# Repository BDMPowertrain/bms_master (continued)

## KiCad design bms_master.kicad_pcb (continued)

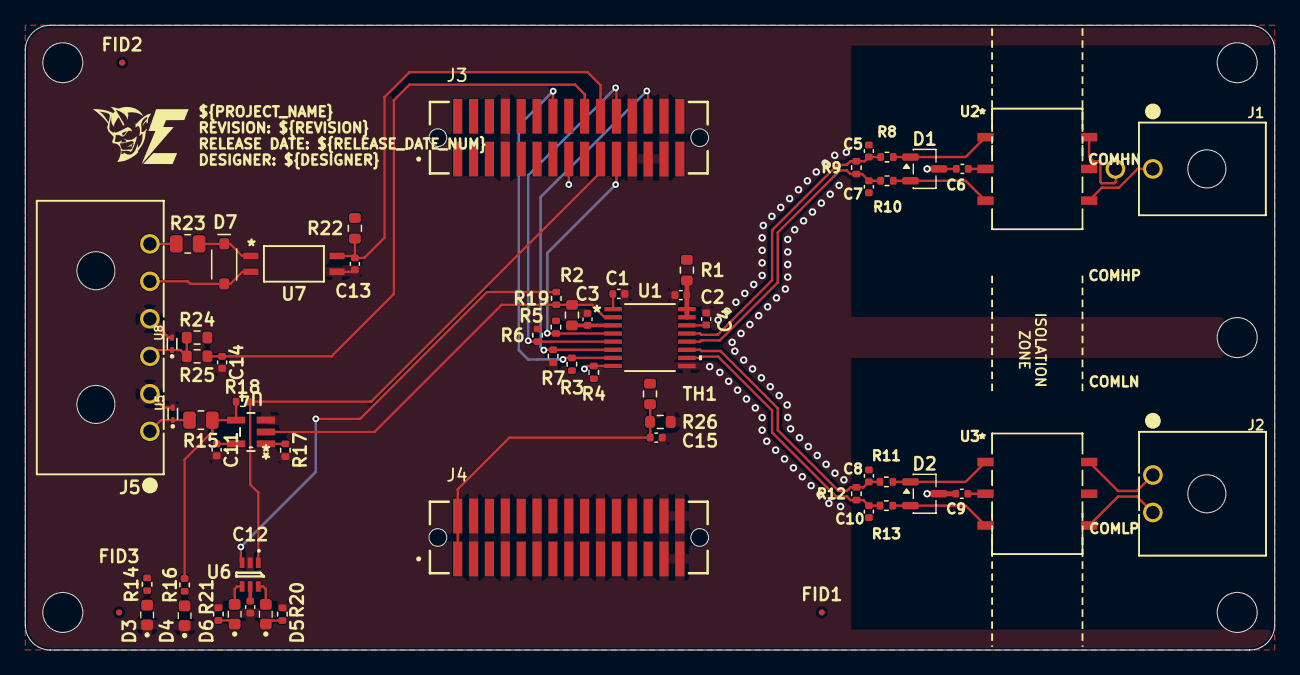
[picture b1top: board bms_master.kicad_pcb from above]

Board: 4 copper layers, 100.0 x 50.0 mm, 72 parts (1 on the bottom side), 45 nets.

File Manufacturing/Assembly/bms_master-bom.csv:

Row,Quantity Per PCB,References,Value,Datasheet,Footprint,Description,Manufacturer,Manufacturer Part Number,Supplier Part Number
1,6,C5 C6 C7 C8 C9 C10,100 pF,https://pim.murata.com/asset/pim4/ceramicCapacitorSMD/GCM155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,C_0402_1005Metric,"100 pF ±5% 50V Ceramic Capacitor C0G, NP0 0402 (1005 Metric)",Murata Electronics,GCM1555C1H101JA16D,
2,2,C13 C14,10 nF,https://yageogroup.com/content/datasheet/asset/file/KEM_C109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,C_0402_1005Metric,10000pf (10 nF or 0.01 uF) ±10% 50V Ceramic Capacitor X7R 0402 (1005 Metric),KEMET,C0402C103K5RECAUTO,
3,5,C2 C3 C11 C12 C15,0.1 µF,https://pim.murata.com/asset/pim4/ceramicCapacitorSMD/GCM155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,C_0402_1005Metric,0.1 uF (100nF) ±10% 50V Ceramic Capacitor X7R 0402 (1005 Metric),Murata Electronics,GCM155R71H104KE02J,
4,2,C1 C4,220 nF,https://pim.murata.com/asset/pim4/ceramicCapacitorSMD/GRM155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,C_0402_1005Metric,0.22 uF (220 nF) ±10% 50V Ceramic Capacitor X5R 0402 (1005 Metric),Murata Electronics,GRM155R61H224KE01D,
5,1,D7,1N4148W,https://diotec.com/request/datasheet/1n4148w.pdf,P35_SOD-123F,Diode 75 V 150mA Surface Mount SOD-123F,Diotec Semiconductor,1N4148W,
6,2,D3 D4,Green,https://optoelectronics.liteon.com/upload/download/DS22-2000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,LED_0603_1608Metric,Green 572nm LED Indication - Discrete 2.15V 0603 (1608 Metric),Lite-On Inc.,LTST-C190KGKT,
7,2,D1 D2,PESD5V0U2BT-QR,https://assets.nexperia.com/documents/data-sheet/PESD5V0U2BT-Q.pdf,SOT-23-3,"Clamp Ipp Tvs Diode Surface Mount TO-236AB, TVS DIODE 5VWM TO236AB",Nexperia USA Inc.,PESD5V0U2BT-QR,
8,2,D5 D6,RED,https://optoelectronics.liteon.com/upload/download/DS-22-99-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,LED_0603_1608Metric,Red 631nm LED Indication - Discrete 2V 0603 (1608 Metric),Lite-On Inc.,LTST-C190KRKT,
9,1,G2,BMD Logo,N/A,BDM_Logo_100mm,Blue Devil Motorsports silkscreen logo.,BMD,BMD Logo,
10,1,G1,SAE Electric logo,N/A,SAE_Electric_Logo_10mm,SAE Electric logo.,BDM,SAE Electric logo,
11,1,J1,0430450200,https://tools.molex.com/pdm_docs/ps/PS-43045.pdf,CONN_SD-43045-001_02_MOL,"Connector Header Through Hole, Right Angle 2 position",Molex,0430450200,
12,1,J2,0436500200,https://www.molex.com/content/dam/molex/molex-dot-com/produc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,CONN_SD-43650-001_02_MOL,"Connector Header Through Hole, Right Angle 2 position 0.118"" (3.00mm)",Molex,0436500200,
13,1,J5,0436500600,https://www.molex.com/content/dam/molex/molex-dot-com/produc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,CONN_SD-43650-001_06_MOL,"Connector Header Through Hole, Right Angle 6 position 0.118"" (3.00mm)",Molex,0436500600,
14,2,J3 J4,TFM-115-02-S-D-WT,https://mm.digikey.com/Volume0/opasdata/d220001/medias/docus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,SAMTEC_TFM-115-02-S-D-WT,"Connector Header Surface Mount 30 position 0.050"" (1.27mm)",SAMTEC Samtec Inc.,TFM-115-02-S-D-WT,
15,1,R1,10,https://www.vishay.com/docs/20035/dcrcwe3.pdf,R_0603_1608Metric,"10 Ohms ±5% 0.1W, 1/10W Chip Resistor 0603 (1608 Metric) Automotive AEC-Q200 Thick Film",Vishay Dale,CRCW060310R0JNEA,
16,4,R8 R10 R11 R13,49.9,https://www.vishay.com/docs/20035/dcrcwe3.pdf,R_0402_1005Metric,"49.9 Ohms ±1% 0.063W, 1/16W Chip Resistor 0402 (1005 Metric) Automotive AEC-Q200 Thick Film",Vishay Dale,CRCW040249R9FKED,
17,1,R15,330,https://www.vishay.com/docs/20035/dcrcwe3.pdf,R_0805_2012Metric,"330 Ohms ±1% 0.125W, 1/8W Chip Resistor 0805 (2012 Metric) Automotive AEC-Q200 Thick Film",Vishay Dale,CRCW0805330RFKEA,
18,6,R9 R12 R14 R16 R20 R21,1k,https://industrial.panasonic.com/cdbs/www-data/pdf/RDA0000/A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,R_0402_1005Metric,"1 kOhms ±1% 0.1W, 1/10W Chip Resistor 0402 (1005 Metric) Automotive AEC-Q200 Thick Film",Panasonic Industry,ERJ-2RKF1001X,
19,6,R3 R4 R7 R17 R18 R19,10k,https://yageogroup.com/content/datasheet/asset/file/PYU-RC_G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,R_0402_1005Metric,"10 kOhms ±5% 0.063W, 1/16W Chip Resistor 0402 (1005 Metric) Moisture Resistant Thick Film",YAGEO,RC0402JR-0710KL,
20,1,R23,10k,https://www.vishay.com/docs/20035/dcrcwe3.pdf,R_0805_2012Metric,"10 kOhms ±1% 0.125W, 1/8W Chip Resistor 0805 (2012 Metric) Automotive AEC-Q200 Thick Film",Vishay Dale,CRCW080510K0FKEA,
21,3,R24 R25 R26,10k,https://www.vishay.com/docs/20035/dcrcwe3.pdf,R_0603_1608Metric,"10 kOhms ±1% 0.1W, 1/10W Chip Resistor 0603 (1608 Metric) Automotive AEC-Q200 Thick Film",Vishay Dale,CRCW060310K0FKEA,
22,1,R22,22k,https://www.vishay.com/docs/20035/dcrcwe3.pdf,R_0603_1608Metric,"22 kOhms ±1% 0.1W, 1/10W Chip Resistor 0603 (1608 Metric) Automotive AEC-Q200 Thick Film",Vishay Dale,CRCW060322K0FKEA,
23,1,R2,100k,https://www.vishay.com/docs/20035/dcrcwe3.pdf,R_0603_1608Metric,"100 kOhms ±1% 0.1W, 1/10W Chip Resistor 0603 (1608 Metric) Automotive AEC-Q200 Thick Film",Vishay Dale,CRCW0603100KFKEA,
24,1,TH1,NCP18XH103F03RB,https://www.murata.com/-/media/webrenewal/products/thermisto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,R_0603_1608Metric,THERMISTOR NTC 10KOHM 3380K 0603,Murata Electronics,NCP18XH103F03RB,
25,1,U1,BQ79600PWRQ1,https://www.ti.com/lit/ds/symlink/bq79600-q1.pdf,SOIC_9600PWQ1_TEX,Automotive SPI/UART communication interface functional-safety compliant with automatic host wakeup.,Texas Instruments,BQ79600PWRQ1,
26,2,U5 U8,ESD9B5.0ST5G,https://www.onsemi.com/pdf/datasheet/esd9b-d.pdf,SODFL1006X40N,Clamp Ipp Tvs Diode Surface Mount SOD-923,onsemi,ESD9B5.0ST5G,
27,2,U2 U3,SM91502ALA-E,https://www.bourns.com/docs/product-datasheets/sm91502ala.pdf,IC6_SM91502ALA-E_BRN,150µH Pulse Transformer 1:1 Surface Mount,Bourns Inc.,SM91502ALA-E,
28,1,U4,SN74LVC1G08QDBVRQ1,https://www.ti.com/general/docs/suppproductinfo.tsp?distId=1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,DBV5,AND Gate IC 1 Channel SOT-23-5,Texas Instruments,SN74LVC1G08QDBVRQ1,
29,1,U6,SN74LVC2G04DCKR,https://www.ti.com/lit/ds/symlink/sn74lvc2g04.pdf?HQS=dis-dk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,DCK0006A_N,Inverter IC 2 Channel SC-70-6,Texas Instruments,SN74LVC2G04DCKR,
30,1,U7,"TLP293(GB-TPL,E",https://toshiba.semicon-storage.com/info/TLP293_datasheet_en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,SO4_TOS,OPTOISOLTR 3.75KV 1CH TRANS 4-SO,Toshiba Semiconductor and Storage,"TLP293(GB-TPL,E",
